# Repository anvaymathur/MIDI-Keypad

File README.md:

# MIDI-Keypad

MIDI Keypad built for Half Life from HackClub. It is hackpad that uses copper touch pads 
that act as buttons for playing notes. A rotary encoder is used to control the octave of the notes.
It can also act like a normal macropad if you chose to, just push down the encoder to switch modes.
The encoder will then act as volume control and the copper touch pads will act like your macro keys.

## Description

This was built following the guide provided by Half Life Hack Club for their music week project. It was a fun
project to make to learn more about music in general because I have never done many music related things before
so learning how MIDI works and how to use it to create music was fun. I added the macropad feature to make it
more functional for me as I do not often create music.

## Features

- Custom PCB
- Neopixel Lights for mode status and while playing notes
- OLED Screen for displaying information
- Copper Touch Pads formed in the shape of a hand to act like ergonomic keys
- EC11 Rotary Encoder for octave control
- Switch modes to use as a generic macropad

## PCB

Custom PCB Made in KiCad. Some footprints and schematics were from Kai Pereira's 
[Hackclub-KiCad-Libraries]("https://github.com/KaiPereira/Hackclub-KiCad-Libraries")

.png)

## Firmware

There is custom firmware written in CircuitPython for controlling all of the components, currently does not include code for different modes, only for the main music mode.

## [BOM](https://docs.google.com/spreadsheets/d/1wcF_mPrZf543xQacLG9ci4BRGrGUtqLDjnGJwcqraqM/edit?usp=sharing)
| Item  | Description | # of Sets | #Pcs / Set | Price / Set (USD) | Item Total Price + Tax & Shipping (USD)| Supplier | URL|
| ----- | ----------- | --------- | ---------- | ----------------- | -------------------------------------- | -------- | -------|
| Megaboard PCB Printing with JLCPCB | PCB | 1 | 5 | $4.00 | $11.33 | JLC PCB | https://kommodo.ai/i/mOOA8IN1I4RNeobWpcTo |
| Waveshare ESP32-S3-Zero | Microcontroller | 1 | 1 | $8.25 | $8.25 | Aliexpress | https://www.aliexpress.com/item/1005012733231291.html?spm=a2g0o.productlist.main.1.47f356e3O78umQ&algo_pvid=a33f782b-47fe-45dc-9786-74fe5942f79a&algo_exp_id=a33f782b-47fe-45dc-9786-74fe5942f79a-0&pdp_ext_f=%7B%22order%22%3A%2263%22%2C%22spu_best_type%22%3A%22price%22%2C%22eval%22%3A%221%22%2C%22fromPage%22%3A%22search%22%7D&pdp_npi=6%40dis%21CAD%2112.18%213.95%21%21%218.50%212.76%21%402101e80f17928740388593327e0f82%2112000059219676552%21sea%21CA%210%21ABX%211%210%21n_tag%3A-29910%3Bd%3Adfeb2caa%3Bm03_new_user%3A-29895%3BpisId%3A5000000218625932&curPageLogUid=9dLDZeafbhZQ&utparam-url=scene%3Asearch%7Cquery_from%3A%7Cx_object_id%3A1005012733231291%7C_p_origin_prod%3A |
| Rotary Encoder EC11 | Rotary Encoder | 1 | 1 | $1.98 | $1.98 | Aliexpress | https://www.aliexpress.com/item/1005006127287538.html?spm=a2g0o.productlist.main.6.14e7639e1W7sGD&algo_pvid=d787a78f-ca16-4b24-b78e-9b4ec4559ee3&algo_exp_id=d787a78f-ca16-4b24-b78e-9b4ec4559ee3-5&pdp_ext_f=%7B%22order%22%3A%22562%22%2C%22eval%22%3A%221%22%2C%22fromPage%22%3A%22search%22%7D&pdp_npi=6%40dis%21USD%212.70%210.99%21%21%212.70%210.99%21%402103094f17928742152533599e100f%2112000035878244634%21sea%21CA%210%21ABX%211%210%21n_tag%3A-29910%3Bd%3Adfeb2caa%3Bm03_new_user%3A-29895%3BpisId%3A5000000218625932&curPageLogUid=TQRes1uqiTr3&utparam-url=scene%3Asearch%7Cquery_from%3A%7Cx_object_id%3A1005006127287538%7C_p_origin_prod%3A |
| SK6812 MINI-E RGB | LED | 1 | 100 | $4.29 | $4.29 | Aliexpress | https://www.aliexpress.com/item/1005007576573654.html?spm=a2g0o.productlist.main.2.1b29677eKDjWdF&algo_pvid=cd1006e3-d410-4b66-8223-8e53e4b6af3e&algo_exp_id=cd1006e3-d410-4b66-8223-8e53e4b6af3e-1&pdp_ext_f=%7B%22order%22%3A%2263%22%2C%22spu_best_type%22%3A%22price%22%2C%22eval%22%3A%221%22%2C%22fromPage%22%3A%22search%22%7D&pdp_npi=6%40dis%21USD%214.29%210.99%21%21%2128.48%216.58%21%402103129017928745977964237e0c7b%2112000061041866515%21sea%21CA%210%21ABX%211%210%21n_tag%3A-29910%3Bd%3Adfeb2caa%3Bm03_new_user%3A-29895%3BpisId%3A5000000218625932&curPageLogUid=jyd2w9d4CFqN&utparam-url=scene%3Asearch%7Cquery_from%3A%7Cx_object_id%3A1005007576573654%7C_p_origin_prod%3A |
| 0.96 in OLED IIC Serial Display Module | OLED Screen | 1 | 1 | $2.68 | $2.68 | Aliexpress | https://www.aliexpress.com/item/1005006141235306.html?spm=a2g0o.productlist.main.1.29c26b0firbgYR&algo_pvid=ea3a9a18-0200-463a-9fe7-0c7b90465e07&algo_exp_id=ea3a9a18-0200-463a-9fe7-0c7b90465e07-0&pdp_ext_f=%7B%22order%22%3A%2226226%22%2C%22spu_best_type%22%3A%22price%22%2C%22eval%22%3A%221%22%2C%22fromPage%22%3A%22search%22%7D&pdp_npi=6%40dis%21USD%212.68%211.19%21%21%2117.80%217.91%21%4021030f4a17928748570274353e0f9c%2112000035944225407%21sea%21CA%210%21ABX%211%210%21n_tag%3A-29910%3Bd%3Adfeb2caa%3Bm03_new_user%3A-29895%3BpisId%3A5000000218625933&curPageLogUid=2CvgUD0ixaiQ&utparam-url=scene%3Asearch%7Cquery_from%3A%7Cx_object_id%3A1005006141235306%7C_p_origin_prod%3A |
| Single Row Female 2.54mm Pinheader Connector | OLED Socket | 1 | 50 | $3.15 | $3.15 | Aliexpress |  https://www.aliexpress.com/item/1005003610378386.html?spm=a2g0o.productlist.main.12.4c5b53814XmSqi&algo_pvid=86a08817-bda5-4dd8-8af6-afcc5c2f45a8&aem_p4p_detail=2026102414242814665487072167430000800614&algo_exp_id=86a08817-bda5-4dd8-8af6-afcc5c2f45a8-11&pdp_ext_f=%7B%22order%22%3A%22948%22%2C%22eval%22%3A%221%22%2C%22fromPage%22%3A%22search%22%7D&pdp_npi=6%40dis%21USD%213.65%211.65%21%21%213.65%211.65%21%402101ca8b17928770687123570e0d8a%2112000026598176397%21sea%21CA%210%21ABX%211%210%21n_tag%3A-29910%3Bd%3Adfeb2caa%3Bm03_new_user%3A-29895%3BpisId%3A5000000218656158&curPageLogUid=8YnDUKAVvz2Y&utparam-url=scene%3Asearch%7Cquery_from%3A%7Cx_object_id%3A1005003610378386%7C_p_origin_prod%3A&search_p4p_id=2026102414242814665487072167430000800614_3 |
| **Grand Total** | *$31.68*

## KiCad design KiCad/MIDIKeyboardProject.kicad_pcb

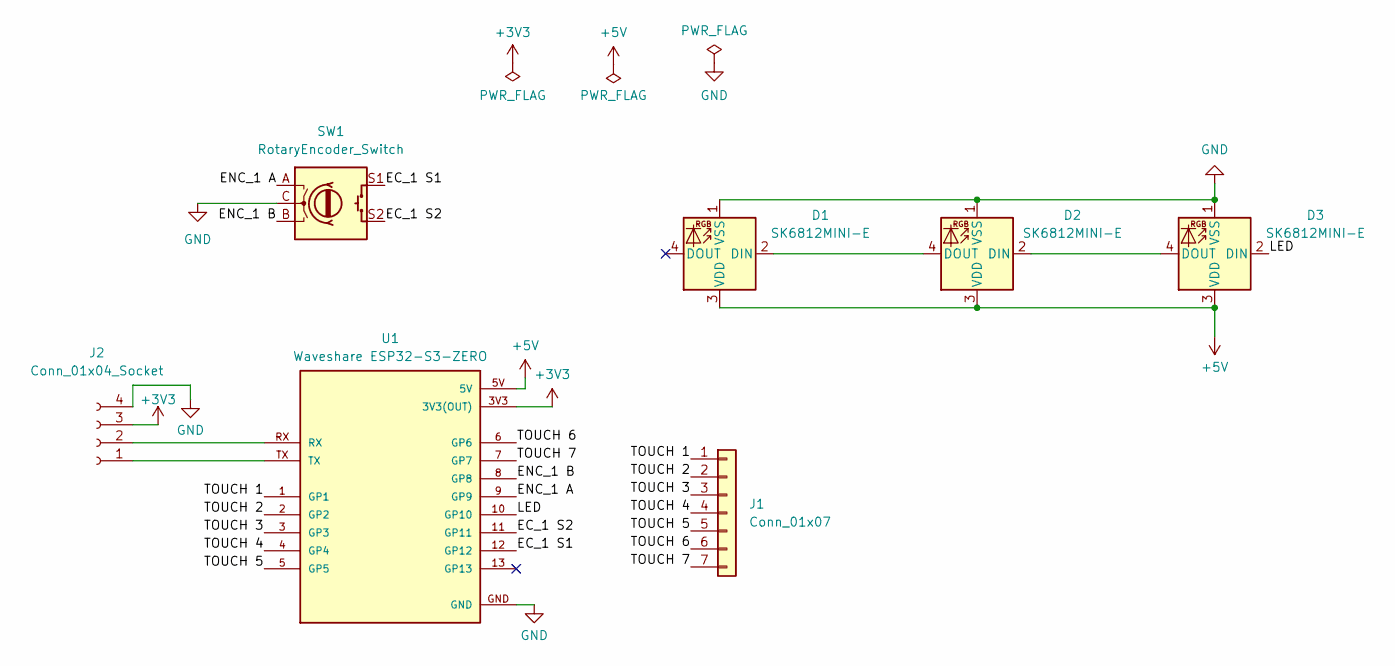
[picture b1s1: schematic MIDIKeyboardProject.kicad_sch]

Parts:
D1, D2, D3: SK6812MINI-E; LED_SK6812MINI-E_3.2x2.8mm_P1.5mm_ReverseMount
J1: Conn_01x07; HandTouch_7
J2: Conn_01x04_Socket; PinSocket_1x04_P2.54mm_Vertical
SW1: RotaryEncoder_Switch; RotaryEncoder_Alps_EC11E-Switch_Vertical_H20mm
U1: Waveshare ESP32-S3-ZERO; Waveshare ESP32-S3-Zero; PARTREV NA

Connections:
+3V3: J2.3, U1.3V3 (3V3(OUT))
+5V: D1.3 (VDD), D2.3 (VDD), D3.3 (VDD), U1.5V
/EC_1 S1: SW1.S1, U1.12 (GP12)
/EC_1 S2: SW1.S2, U1.11 (GP11)
/ENC_1 A: SW1.A, U1.9 (GP9)
/ENC_1 B: SW1.B, U1.8 (GP8)
/LED: D3.2 (DIN), U1.10 (GP10)
/TOUCH 1: J1.1, U1.1 (GP1)
/TOUCH 2: J1.2, U1.2 (GP2)
/TOUCH 3: J1.3, U1.3 (GP3)
/TOUCH 4: J1.4, U1.4 (GP4)
/TOUCH 5: J1.5, U1.5 (GP5)
/TOUCH 6: J1.6, U1.6 (GP6)
/TOUCH 7: J1.7, U1.7 (GP7)
GND: D1.1 (VSS), D2.1 (VSS), D3.1 (VSS), J2.4, SW1.C, U1.GND
unnamed: D1.2 (DIN), D2.4 (DOUT)
unnamed: D2.2 (DIN), D3.4 (DOUT)
unnamed: J2.1, U1.TX
unnamed: J2.2, U1.RX

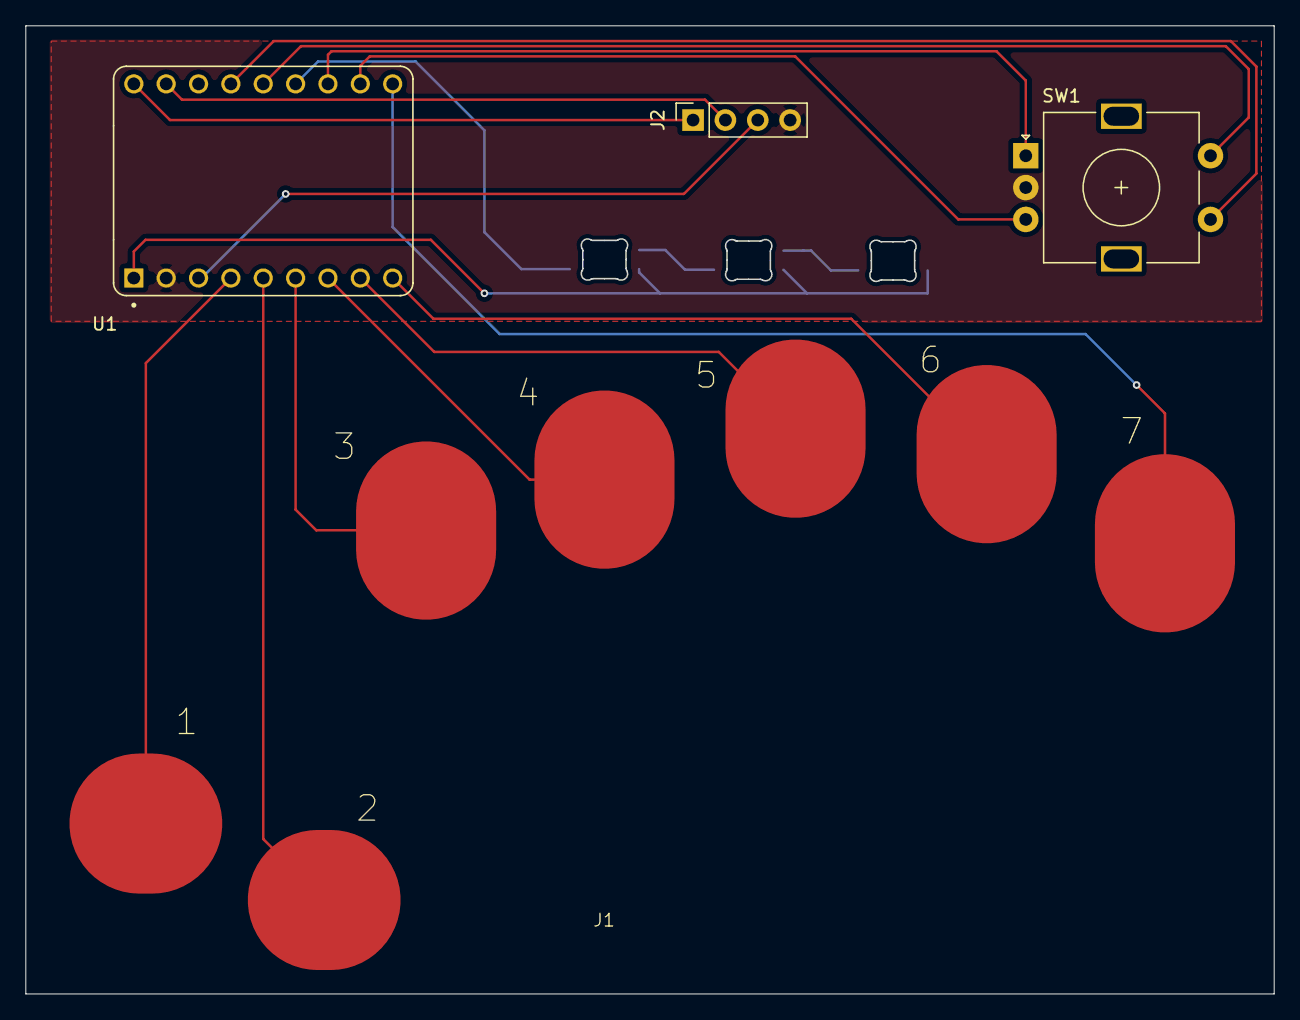
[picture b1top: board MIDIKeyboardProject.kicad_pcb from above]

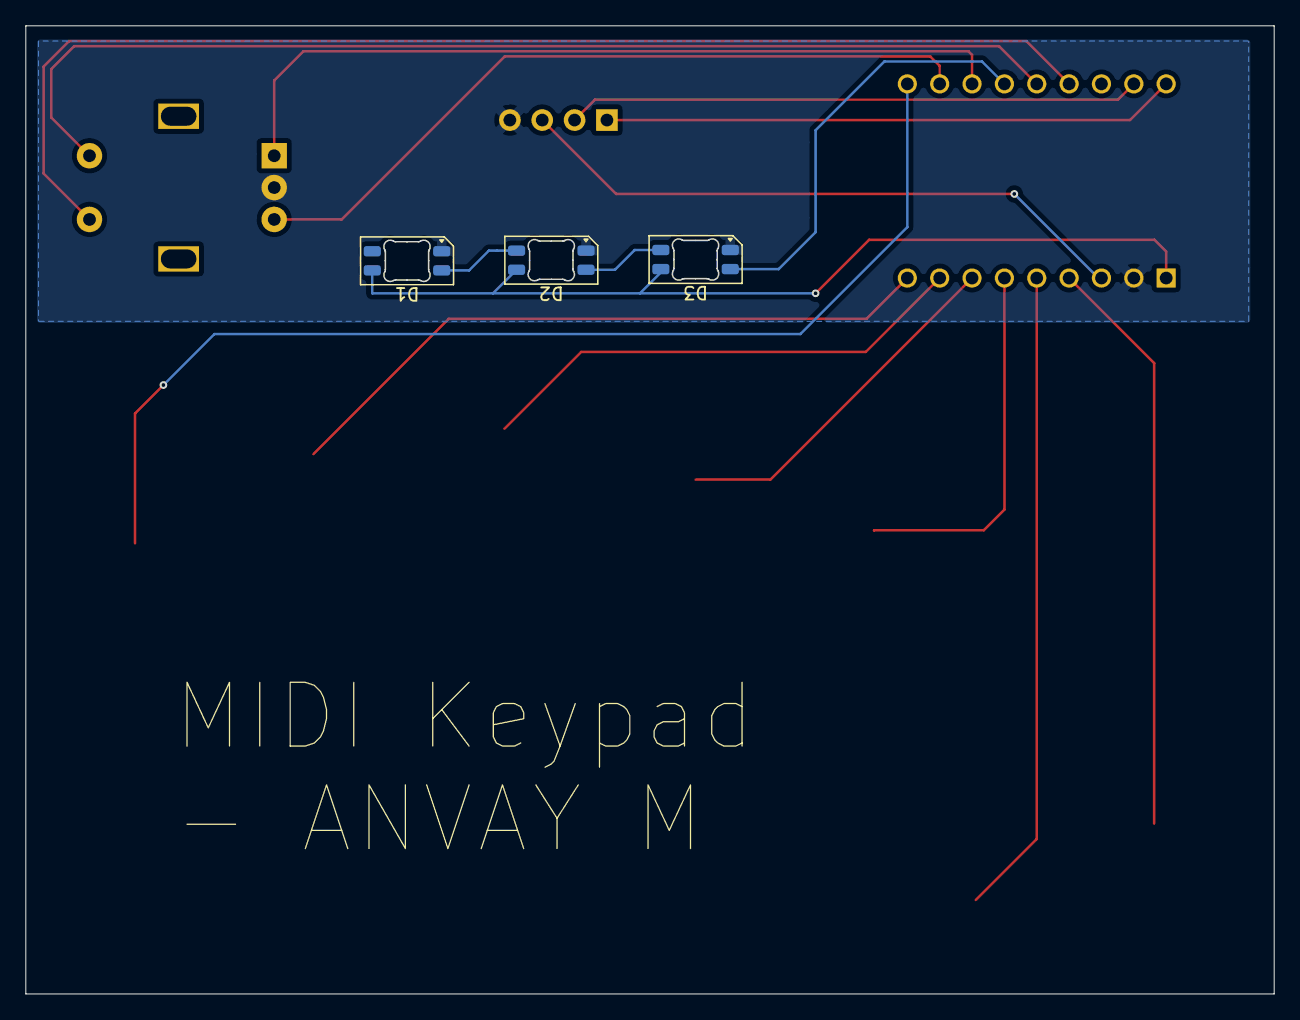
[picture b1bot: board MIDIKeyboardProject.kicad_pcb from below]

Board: 2 copper layers, 98.0 x 76.0 mm, 7 parts (3 on the bottom side), 19 nets.

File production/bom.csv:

Designator,Footprint,Quantity,Value,LCSC Part #
"D1, D2, D3",LED_SK6812MINI-E_3.2x2.8mm_P1.5mm_ReverseMount,3,SK6812MINI-E,
J1,HandTouch_7,1,Conn_01x07,
J2,PinSocket_1x04_P2.54mm_Vertical,1,Conn_01x04_Socket,
SW1,RotaryEncoder_Alps_EC11E-Switch_Vertical_H20mm,1,RotaryEncoder_Switch,
U1,Waveshare ESP32-S3-Zero,1,Waveshare ESP32-S3-ZERO,
